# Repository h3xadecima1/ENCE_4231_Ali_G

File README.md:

# ENCE_4231_Ali_G
Embedded Systems

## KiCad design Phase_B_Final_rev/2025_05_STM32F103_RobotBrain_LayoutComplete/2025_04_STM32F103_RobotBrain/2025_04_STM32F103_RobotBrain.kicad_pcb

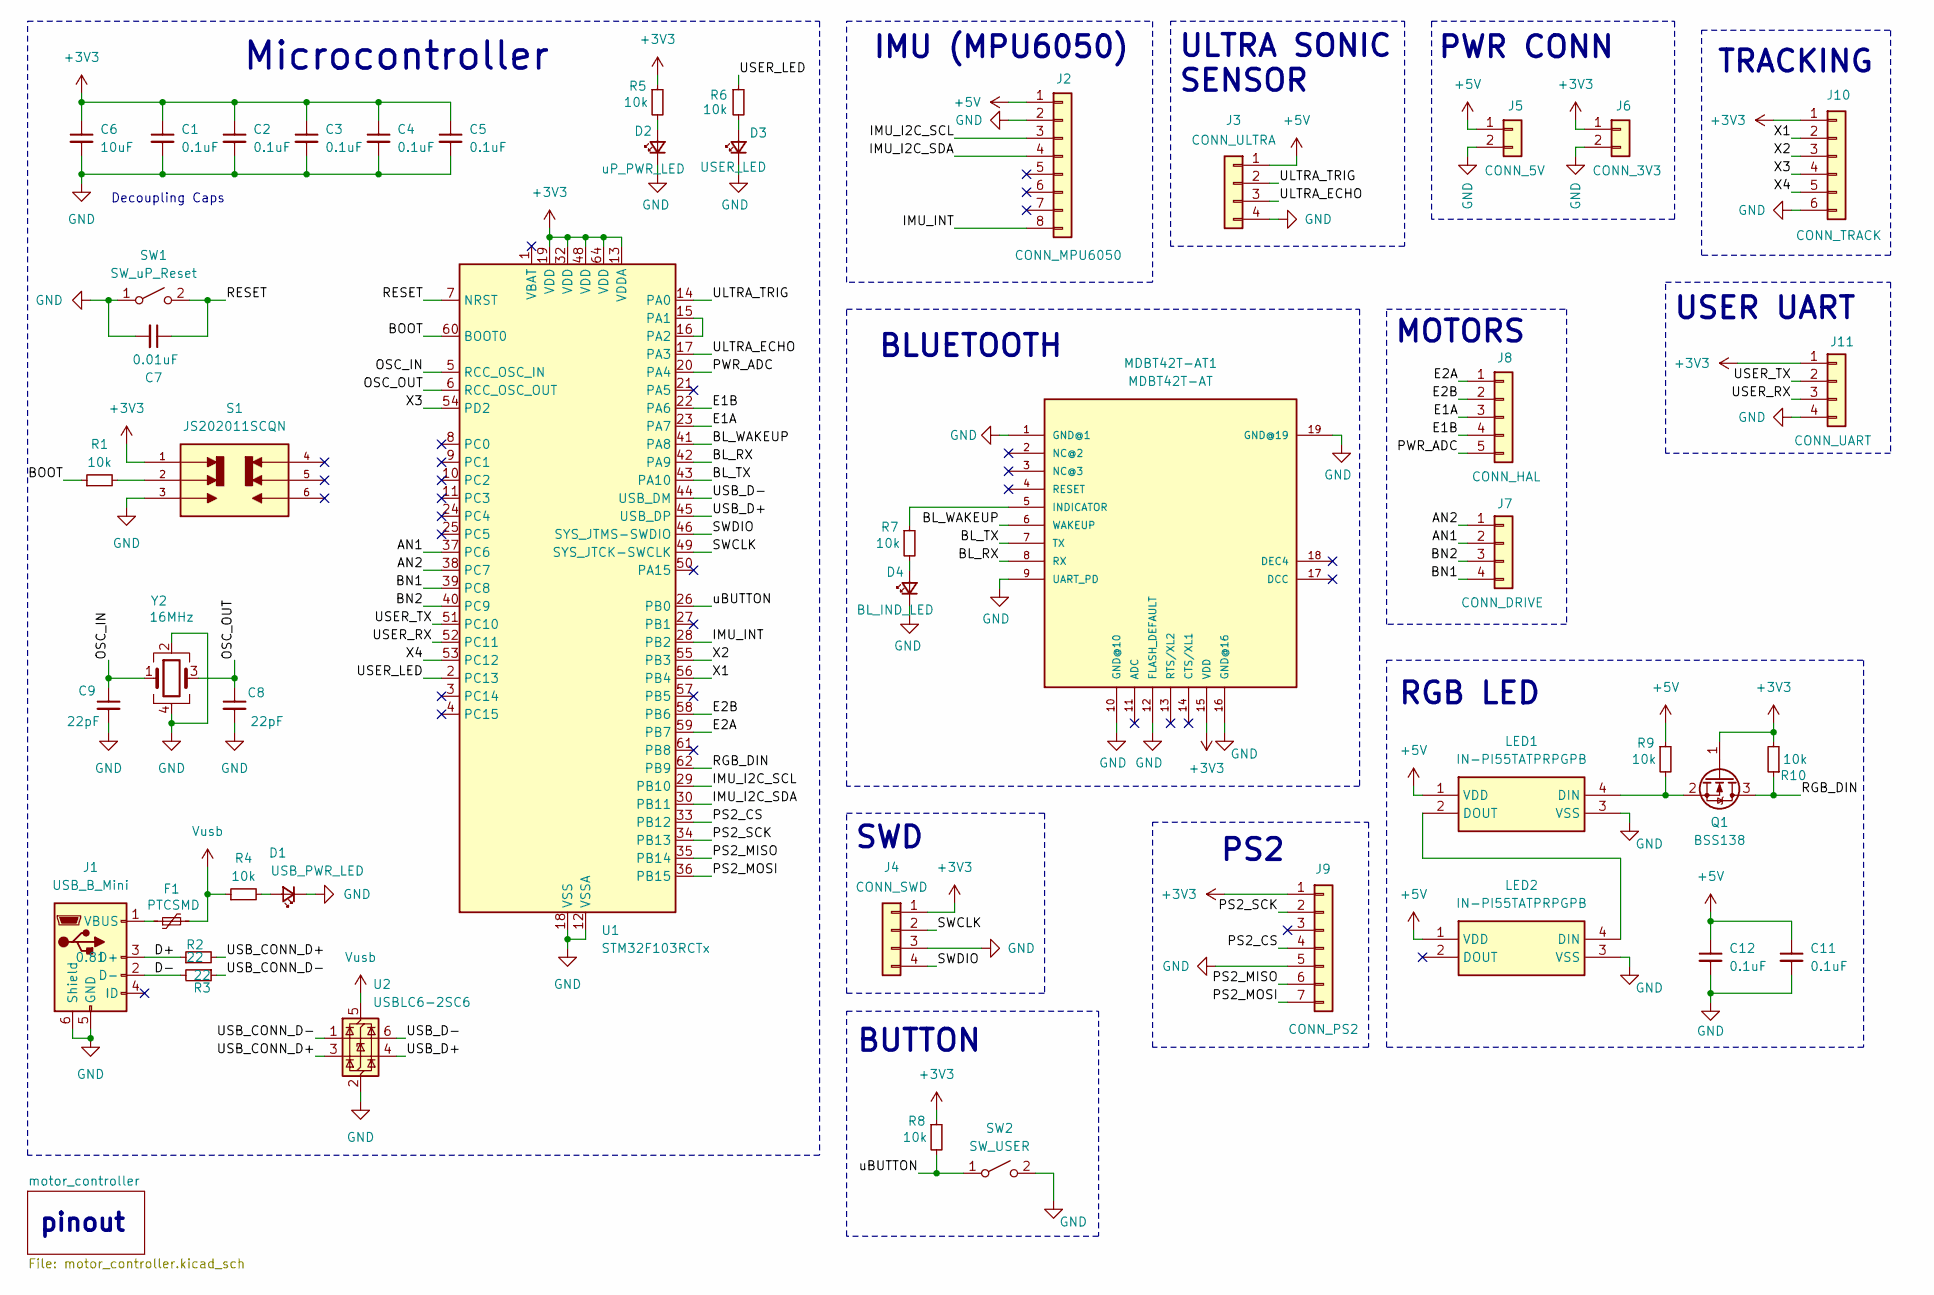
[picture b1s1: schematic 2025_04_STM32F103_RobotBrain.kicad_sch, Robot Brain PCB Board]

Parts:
C1, C2, C3, C4, C5, C11, C12: 0.1uF; C_0805_2012Metric_Pad1.18x1.45mm_HandSolder; Mfr #P KAM21BR71H104JT
C6: 10uF; C_0805_2012Metric_Pad1.18x1.45mm_HandSolder; Mfr #P LMK212ABJ106KG-T
C7: 0.01uF; C_0805_2012Metric_Pad1.18x1.45mm_HandSolder; Mfr #P KAF21BR72A103JT
C8, C9: 22pF; C_0805_2012Metric_Pad1.18x1.45mm_HandSolder; Mfr #P 0805ZA220JAT2A
D1: USB_PWR_LED; LED_0805_2012Metric_Pad1.15x1.40mm_HandSolder; Mfr #P 150080VS75000
D2: uP_PWR_LED; LED_0805_2012Metric_Pad1.15x1.40mm_HandSolder; Mfr #P 150080VS75000
D3: USER_LED; LED_0805_2012Metric_Pad1.15x1.40mm_HandSolder; Mfr #P 150080RS75000
D4: BL_IND_LED; LED_0805_2012Metric_Pad1.15x1.40mm_HandSolder; Mfr #P 150080VS75000
F1: PTCSMD; Fuse_0805_2012Metric_Pad1.15x1.40mm_HandSolder; Mfr #P 0ZCK0050AF2E
J1: USB_B_Mini; USB_Mini-B_Lumberg_2486_01_Horizontal; Mfr #P UJ2-MBH-4-SMT-TR
J2: CONN_MPU6050; PinSocket_1x08_P2.54mm_Vertical
J3: CONN_ULTRA; PinSocket_1x04_P2.54mm_Vertical
J4: CONN_SWD; PinSocket_1x04_P2.54mm_Vertical
J5: CONN_5V; JST_XH_B2B-XH-A_1x02_P2.50mm_Vertical
J6: CONN_3V3; JST_XH_B2B-XH-A_1x02_P2.50mm_Vertical
J7: CONN_DRIVE; JST_XH_B4B-XH-A_1x04_P2.50mm_Vertical
J8: CONN_HAL; JST_XH_B5B-XH-A_1x05_P2.50mm_Vertical
J9: CONN_PS2; PinHeader_1x07_P2.54mm_Vertical
J10: CONN_TRACK; JST_XH_B6B-XH-A_1x06_P2.50mm_Vertical
J11: CONN_UART; JST_XH_B4B-XH-A_1x04_P2.50mm_Vertical
LED1, LED2: IN-PI55TATPRPGPB; INPI55TATPRPGPB; Manufacturer_Part_Number IN-PI55TATPRPGPB; Mouser Part Number 743-IN-PI55TATPRPGPB
MDBT42T-AT1: MDBT42T-AT; MDBT42T
Q1: BSS138; SOT-23; Mfr #P BSS138
R1, R4, R5, R6, R7, R8, R9, R10: 10k; R_0805_2012Metric_Pad1.20x1.40mm_HandSolder; Mfr #P RK73B2ATTE103J
R2, R3: 22; R_0805_2012Metric_Pad1.20x1.40mm_HandSolder; Mfr #P RC0805FR-7W22RL
S1: JS202011SCQN; SW_uP_Boot; PARTREV 26 May 22
SW1: SW_uP_Reset; Mfr #P 434121025816
SW2: SW_USER; SW_SPST_PTS647_Sx50; Mfr #P TL3305BF100QG
U1: STM32F103RCTx; LQFP-64_10x10mm_P0.5mm; Mfr #P STM32F103RCT6
U2: USBLC6-2SC6; SOT-23-6; Mfr #P USBLC6-2SC6
Y2: 16MHz; Crystal_SMD_Abracon_ABM8G-4Pin_3.2x2.5mm; Mfr #P ABM8-16.000MHZ-D1X-T

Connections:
+3V3: C1.1, C2.1, C3.1, C4.1, C5.1, C6.1, J4.1, J6.1, J9.1, J10.1, J11.1, MDBT42T-AT1.15 (VDD), Q1.1 (G), R5.1, R8.1, R10.2, S1.1, U1.13 (VDDA), U1.19 (VDD), U1.32 (VDD), U1.48 (VDD), U1.64 (VDD)
+5V: C11.1, C12.1, J2.1, J3.1, J5.1, LED1.1 (VDD), LED2.1 (VDD), R9.1
/AN1: J7.2, U1.37 (PC6)
/AN2: J7.1, U1.38 (PC7)
/BL_RX: MDBT42T-AT1.8 (RX), U1.42 (PA9)
/BL_TX: MDBT42T-AT1.7 (TX), U1.43 (PA10)
/BL_WAKEUP: MDBT42T-AT1.6 (WAKEUP), U1.41 (PA8)
/BN1: J7.4, U1.39 (PC8)
/BN2: J7.3, U1.40 (PC9)
/BOOT: R1.1, U1.60 (BOOT0)
/D+: J1.3 (D+), R2.1
/D-: J1.2 (D-), R3.2
/E1A: J8.3, U1.23 (PA7)
/E1B: J8.4, U1.22 (PA6)
/E2A: J8.1, U1.59 (PB7)
/E2B: J8.2, U1.58 (PB6)
/IMU_I2C_SCL: J2.3, U1.29 (PB10)
/IMU_I2C_SDA: J2.4, U1.30 (PB11)
/IMU_INT: J2.8, U1.28 (PB2)
/OSC_IN: C9.1, U1.5 (RCC_OSC_IN), Y2.1
/OSC_OUT: C8.1, U1.6 (RCC_OSC_OUT), Y2.3
/PS2_CS: J9.4, U1.33 (PB12)
/PS2_MISO: J9.6, U1.35 (PB14)
/PS2_MOSI: J9.7, U1.36 (PB15)
/PS2_SCK: J9.2, U1.34 (PB13)
/PWR_ADC: J8.5, U1.20 (PA4)
/RESET: C7.1, SW1.2 (B), U1.7 (NRST)
/RGB_DIN: Q1.3 (D), R10.1, U1.62 (PB9)
/SWCLK: J4.2, U1.49 (SYS_JTCK-SWCLK)
/SWDIO: J4.4, U1.46 (SYS_JTMS-SWDIO)
/ULTRA_ECHO: J3.3, U1.17 (PA3)
/ULTRA_TRIG: J3.2, U1.14 (PA0)
/USB_CONN_D+: R2.2, U2.3 (I/O2)
/USB_CONN_D-: R3.1, U2.1 (I/O1)
/USB_D+: U1.45 (USB_DP), U2.4 (I/O2)
/USB_D-: U1.44 (USB_DM), U2.6 (I/O1)
/USER_LED: R6.1, U1.2 (PC13)
/USER_RX: J11.3, U1.52 (PC11)
/USER_TX: J11.2, U1.51 (PC10)
/X1: J10.2, U1.56 (PB4)
/X2: J10.3, U1.55 (PB3)
/X3: J10.4, U1.54 (PD2)
/X4: J10.5, U1.53 (PC12)
/uBUTTON: R8.2, SW2.1 (A), U1.26 (PB0)
GND: C1.2, C2.2, C3.2, C4.2, C5.2, C6.2, C7.2, C8.2, C9.2, C11.2, C12.2, D1.1 (K), D2.1 (K), D3.1 (K), D4.1 (K), J1.5 (GND), J1.6 (Shield), J2.2, J3.4, J4.3, J5.2, J6.2, J9.5, J10.6, J11.4, LED1.3 (VSS), LED2.3 (VSS), MDBT42T-AT1.1 (GND@1), MDBT42T-AT1.9 (UART_PD), MDBT42T-AT1.10 (GND@10), MDBT42T-AT1.12 (FLASH_DEFAULT), MDBT42T-AT1.16 (GND@16), MDBT42T-AT1.19 (GND@19), S1.3, SW1.1 (A), SW2.2 (B), U1.12 (VSSA), U1.18 (VSS), U1.31 (VSS), U1.47 (VSS), U1.63 (VSS), U2.2 (GND), Y2.2, Y2.4
unnamed: D1.2 (A), R4.2
unnamed: D2.2 (A), R5.2
unnamed: D3.2 (A), R6.2
unnamed: D4.2 (A), R7.2
unnamed: F1.1, J1.1 (VBUS)
unnamed: LED1.4 (DIN), Q1.2 (S), R9.2
unnamed: LED1.2 (DOUT), LED2.4 (DIN)
unnamed: MDBT42T-AT1.5 (INDICATOR), R7.1
unnamed: R1.2, S1.2
unnamed: U1.15 (PA1), U1.16 (PA2)
Vusb: F1.2, R4.1, U2.5 (VBUS)

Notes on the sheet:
PWR CONN
ULTRA SONIC SENSOR
Decoupling Caps
BUTTON
MOTORS
PS2
RGB LED
Microcontroller
TRACKING
pinout
IMU (MPU6050)
SWD
USER UART
BLUETOOTH

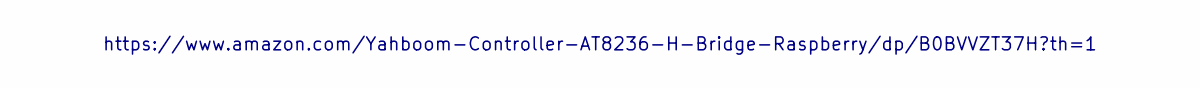
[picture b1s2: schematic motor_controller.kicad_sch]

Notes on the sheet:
https://www.amazon.com/Yahboom-Controller-AT8236-H-Bridge-Raspberry/dp/B0BVVZT37H?th=1

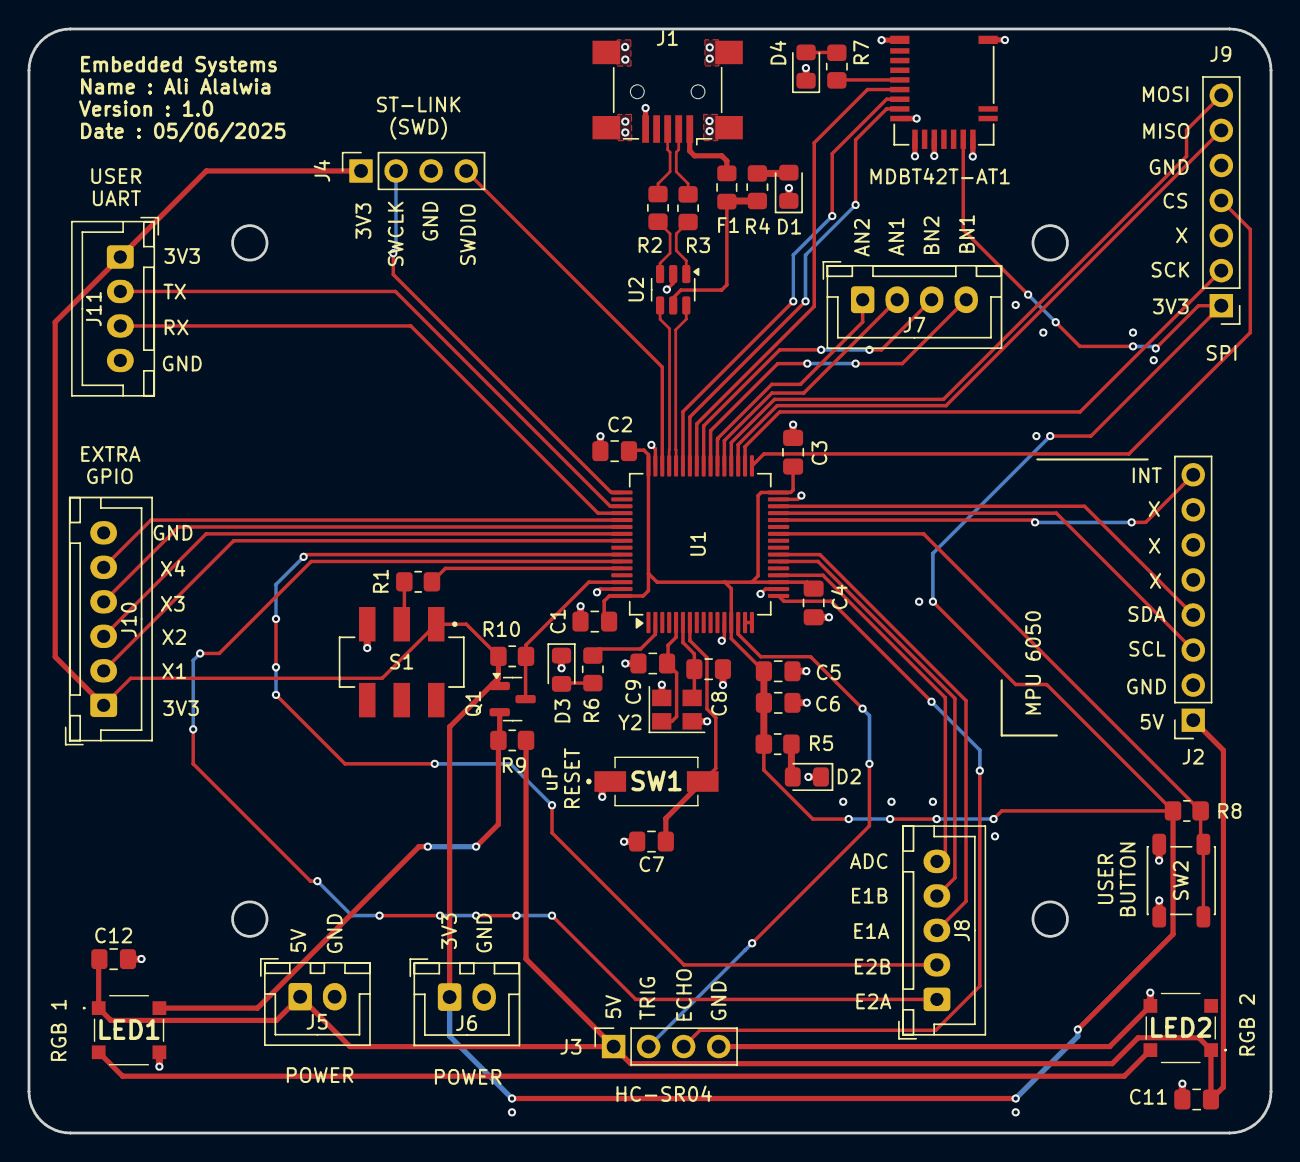
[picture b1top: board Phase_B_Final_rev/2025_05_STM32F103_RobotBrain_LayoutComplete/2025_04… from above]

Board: 2 copper layers, 90.0 x 80.0 mm, 47 parts (0 on the bottom side), 56 nets.

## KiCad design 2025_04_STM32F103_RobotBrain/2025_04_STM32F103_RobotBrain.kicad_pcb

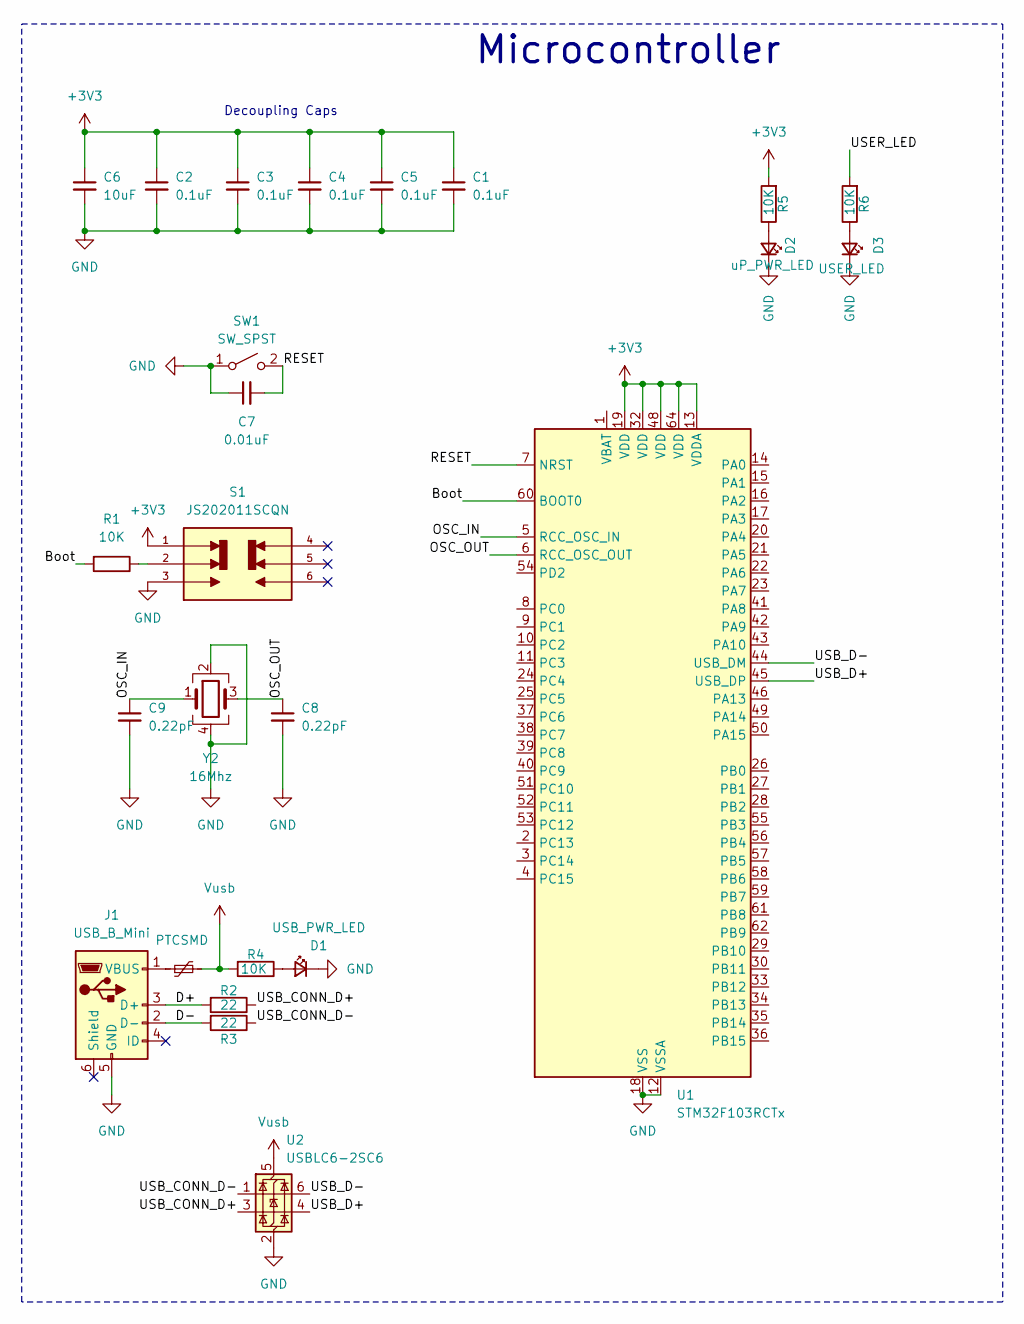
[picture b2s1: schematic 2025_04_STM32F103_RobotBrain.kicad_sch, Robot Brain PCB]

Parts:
C1, C2, C3, C4, C5: 0.1uF; C_0805_2012Metric_Pad1.18x1.45mm_HandSolder; Mfr #P KAM21BR71H104JT
C6: 10uF; C_0805_2012Metric_Pad1.18x1.45mm_HandSolder; Mfr #P LMK212ABJ106KG-T
C7: 0.01uF; C_0805_2012Metric_Pad1.18x1.45mm_HandSolder; Mfr #P KAF21BR72A103JT
C8, C9: 0.22pF; C_0805_2012Metric_Pad1.18x1.45mm_HandSolder; Mfr #P 0805YA220JAT2A
D1: USB_PWR_LED; LED_0805_2012Metric; Mfr# 150080VS75000
D2: uP_PWR_LED; LED_0805_2012Metric; Mfr# 150080VS75000
D3: USER_LED; LED_0805_2012Metric; Mfr# 150080VS75000
F1: PTCSMD; Fuse_0805_2012Metric_Pad1.15x1.40mm_HandSolder; Mfr# 0ZCK0050AF2E
J1: USB_B_Mini; USB_Mini-B_Lumberg_2486_01_Horizontal
R1, R4, R5, R6: 10K; R_0805_2012Metric_Pad1.20x1.40mm_HandSolder; Mfr# RK73B2ATTE103J
R2, R3: 22; R_0805_2012Metric_Pad1.20x1.40mm_HandSolder; Mfr# RK73B2ATTE103J
S1: JS202011SCQN; SW_up_Boot; PARTREV 26 May 22
SW1: SW_SPST; SW_uP_Reset
U1: STM32F103RCTx; LQFP-64_10x10mm_P0.5mm; Mfg #P STM32F103RCT6
U2: USBLC6-2SC6; SOT-23-6
Y2: 16Mhz; Crystal_SMD_Abracon_ABM8G-4Pin_3.2x2.5mm; Mfr# ABM8-16.000MHZ-D1X-T

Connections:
+3V3: C1.1, C2.1, C3.1, C4.1, C5.1, C6.1, R5.2, S1.1, U1.13 (VDDA), U1.19 (VDD), U1.32 (VDD), U1.48 (VDD), U1.64 (VDD)
/Boot: R1.2, U1.60 (BOOT0)
/D+: J1.3 (D+), R2.2
/D-: J1.2 (D-), R3.2
/OSC_IN: C9.1, U1.5 (RCC_OSC_IN), Y2.1
/OSC_OUT: C8.1, U1.6 (RCC_OSC_OUT), Y2.3
/RESET: C7.2, SW1.2 (B), U1.7 (NRST)
/USB_CONN_D+: R2.1, U2.3 (I/O2)
/USB_CONN_D-: R3.1, U2.1 (I/O1)
/USB_D+: U1.45 (USB_DP), U2.4 (I/O2)
/USB_D-: U1.44 (USB_DM), U2.6 (I/O1)
/USER_LED: R6.2
GND: C1.2, C2.2, C3.2, C4.2, C5.2, C6.2, C7.1, C8.2, C9.2, D1.1 (K), D2.1 (K), D3.1 (K), J1.5 (GND), S1.3, SW1.1 (A), U1.12 (VSSA), U1.18 (VSS), U1.31 (VSS), U1.47 (VSS), U1.63 (VSS), U2.2 (GND), Y2.2, Y2.4
unnamed: D1.2 (A), R4.1
unnamed: D2.2 (A), R5.1
unnamed: D3.2 (A), R6.1
unnamed: F1.1, J1.1 (VBUS)
unnamed: R1.1, S1.2
Vusb: F1.2, R4.2, U2.5 (VBUS)

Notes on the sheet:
Decoupling Caps
Microcontroller

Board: 2 copper layers, 25 parts (0 on the bottom side), 18 nets, no tracks yet.

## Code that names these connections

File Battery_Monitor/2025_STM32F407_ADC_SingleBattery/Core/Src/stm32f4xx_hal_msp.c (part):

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
    __HAL_RCC_GPIOA_CLK_ENABLE();
    /**ADC1 GPIO Configuration
    PA1     ------> ADC1_IN1
    PA4     ------> ADC1_IN4
    */
    GPIO_InitStruct.Pin = GPIO_PIN_1|GPIO_PIN_4;
    GPIO_InitStruct.Mode = GPIO_MODE_ANALOG;
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    __HAL_RCC_ADC1_CLK_DISABLE();

    /**ADC1 GPIO Configuration
    PA1     ------> ADC1_IN1
    PA4     ------> ADC1_IN4
    */
    HAL_GPIO_DeInit(GPIOA, GPIO_PIN_1|GPIO_PIN_4);

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
    __HAL_RCC_GPIOB_CLK_ENABLE();
    /**I2C1 GPIO Configuration
    PB6     ------> I2C1_SCL
    PB9     ------> I2C1_SDA
    */
    GPIO_InitStruct.Pin = Audio_SCL_Pin|Audio_SDA_Pin;
    GPIO_InitStruct.Mode = GPIO_MODE_AF_OD;
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    __HAL_RCC_I2C1_CLK_DISABLE();

    /**I2C1 GPIO Configuration
    PB6     ------> I2C1_SCL
    PB9     ------> I2C1_SDA
    */
    HAL_GPIO_DeInit(Audio_SCL_GPIO_Port, Audio_SCL_Pin);

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    __HAL_RCC_GPIOA_CLK_ENABLE();
    /**SPI1 GPIO Configuration
    PA5     ------> SPI1_SCK
    PA6     ------> SPI1_MISO
    PA7     ------> SPI1_MOSI
    */
    GPIO_InitStruct.Pin = SPI1_SCK_Pin|SPI1_MISO_Pin|SPI1_MOSI_Pin;
    GPIO_InitStruct.Mode = GPIO_MODE_AF_PP;
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
    /**SPI1 GPIO Configuration
    PA5     ------> SPI1_SCK
    PA6     ------> SPI1_MISO
    PA7     ------> SPI1_MOSI
    */
    HAL_GPIO_DeInit(GPIOA, SPI1_SCK_Pin|SPI1_MISO_Pin|SPI1_MOSI_Pin);

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
    __HAL_RCC_GPIOA_CLK_ENABLE();
    /**TIM1 GPIO Configuration
    PA8     ------> TIM1_CH1
    */
    GPIO_InitStruct.Pin = GPIO_PIN_8;
    GPIO_InitStruct.Mode = GPIO_MODE_AF_PP;
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
    __HAL_RCC_GPIOA_CLK_ENABLE();
    /**USART2 GPIO Configuration
    PA2     ------> USART2_TX
    PA3     ------> USART2_RX
    */
    GPIO_InitStruct.Pin = GPIO_PIN_2|GPIO_PIN_3;
    GPIO_InitStruct.Mode = GPIO_MODE_AF_PP;
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    __HAL_RCC_USART2_CLK_DISABLE();

    /**USART2 GPIO Configuration
    PA2     ------> USART2_TX
    PA3     ------> USART2_RX
    */
    HAL_GPIO_DeInit(GPIOA, GPIO_PIN_2|GPIO_PIN_3);

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
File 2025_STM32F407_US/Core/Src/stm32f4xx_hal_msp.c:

/* USER CODE BEGIN Header */
/**
  ******************************************************************************
  * @file         stm32f4xx_hal_msp.c
  * @brief        This file provides code for the MSP Initialization
  *               and de-Initialization codes.
  ******************************************************************************
  * @attention
  *
  * Copyright (c) 2025 STMicroelectronics.
  * All rights reserved.
  *
  * This software is licensed under terms that can be found in the LICENSE file
  * in the root directory of this software component.
  * If no LICENSE file comes with this software, it is provided AS-IS.
  *
  ******************************************************************************
  */
/* USER CODE END Header */

/* Includes ------------------------------------------------------------------*/
#include "main.h"
/* USER CODE BEGIN Includes */

/* USER CODE END Includes */

/* Private typedef -----------------------------------------------------------*/
/* USER CODE BEGIN TD */

/* USER CODE END TD */

/* Private define ------------------------------------------------------------*/
/* USER CODE BEGIN Define */

/* USER CODE END Define */

/* Private macro -------------------------------------------------------------*/
/* USER CODE BEGIN Macro */

/* USER CODE END Macro */

/* Private variables ---------------------------------------------------------*/
/* USER CODE BEGIN PV */

/* USER CODE END PV */

/* Private function prototypes -----------------------------------------------*/
/* USER CODE BEGIN PFP */

/* USER CODE END PFP */

/* External functions --------------------------------------------------------*/
/* USER CODE BEGIN ExternalFunctions */

/* USER CODE END ExternalFunctions */

/* USER CODE BEGIN 0 */

/* USER CODE END 0 */

void HAL_TIM_MspPostInit(TIM_HandleTypeDef *htim);
                    /**
  * Initializes the Global MSP.
  */
void HAL_MspInit(void)
{

  /* USER CODE BEGIN MspInit 0 */

  /* USER CODE END MspInit 0 */

  __HAL_RCC_SYSCFG_CLK_ENABLE();
  __HAL_RCC_PWR_CLK_ENABLE();

  HAL_NVIC_SetPriorityGrouping(NVIC_PRIORITYGROUP_0);

  /* System interrupt init*/

  /* USER CODE BEGIN MspInit 1 */

  /* USER CODE END MspInit 1 */
}

/**
  * @brief TIM_Base MSP Initialization
  * This function configures the hardware resources used in this example
  * @param htim_base: TIM_Base handle pointer
  * @retval None
  */
void HAL_TIM_Base_MspInit(TIM_HandleTypeDef* htim_base)
{
  GPIO_InitTypeDef GPIO_InitStruct = {0};
  if(htim_base->Instance==TIM8)
  {
    /* USER CODE BEGIN TIM8_MspInit 0 */

    /* USER CODE END TIM8_MspInit 0 */
    /* Peripheral clock enable */
    __HAL_RCC_TIM8_CLK_ENABLE();

    __HAL_RCC_GPIOC_CLK_ENABLE();
    /**TIM8 GPIO Configuration
    PC6     ------> TIM8_CH1
    PC7     ------> TIM8_CH2
    */
    GPIO_InitStruct.Pin = ECHO_Pin|GPIO_PIN_7;
    GPIO_InitStruct.Mode = GPIO_MODE_AF_PP;
    GPIO_InitStruct.Pull = GPIO_NOPULL;
    GPIO_InitStruct.Speed = GPIO_SPEED_FREQ_LOW;
    GPIO_InitStruct.Alternate = GPIO_AF3_TIM8;
    HAL_GPIO_Init(GPIOC, &GPIO_InitStruct);

    /* USER CODE BEGIN TIM8_MspInit 1 */

    /* USER CODE END TIM8_MspInit 1 */
  }
  else if(htim_base->Instance==TIM11)
  {
    /* USER CODE BEGIN TIM11_MspInit 0 */

    /* USER CODE END TIM11_MspInit 0 */
    /* Peripheral clock enable */
    __HAL_RCC_TIM11_CLK_ENABLE();
    /* TIM11 interrupt Init */
    HAL_NVIC_SetPriority(TIM1_TRG_COM_TIM11_IRQn, 0, 0);
    HAL_NVIC_EnableIRQ(TIM1_TRG_COM_TIM11_IRQn);
    /* USER CODE BEGIN TIM11_MspInit 1 */

    /* USER CODE END TIM11_MspInit 1 */
  }

}

void HAL_TIM_MspPostInit(TIM_HandleTypeDef* htim)
{
  GPIO_InitTypeDef GPIO_InitStruct = {0};
  if(htim->Instance==TIM11)
  {
    /* USER CODE BEGIN TIM11_MspPostInit 0 */

    /* USER CODE END TIM11_MspPostInit 0 */

    __HAL_RCC_GPIOB_CLK_ENABLE();
    /**TIM11 GPIO Configuration
    PB9     ------> TIM11_CH1
    */
    GPIO_InitStruct.Pin = TRIG_Pin;
    GPIO_InitStruct.Mode = GPIO_MODE_AF_PP;
    GPIO_InitStruct.Pull = GPIO_NOPULL;
    GPIO_InitStruct.Speed = GPIO_SPEED_FREQ_LOW;
    GPIO_InitStruct.Alternate = GPIO_AF3_TIM11;
    HAL_GPIO_Init(TRIG_GPIO_Port, &GPIO_InitStruct);

    /* USER CODE BEGIN TIM11_MspPostInit 1 */

    /* USER CODE END TIM11_MspPostInit 1 */
  }

}
/**
  * @brief TIM_Base MSP De-Initialization
  * This function freeze the hardware resources used in this example
  * @param htim_base: TIM_Base handle pointer
  * @retval None
  */
void HAL_TIM_Base_MspDeInit(TIM_HandleTypeDef* htim_base)
{
  if(htim_base->Instance==TIM8)
  {
    /* USER CODE BEGIN TIM8_MspDeInit 0 */

    /* USER CODE END TIM8_MspDeInit 0 */
    /* Peripheral clock disable */
    __HAL_RCC_TIM8_CLK_DISABLE();

    /**TIM8 GPIO Configuration
    PC6     ------> TIM8_CH1
    PC7     ------> TIM8_CH2
    */
    HAL_GPIO_DeInit(GPIOC, ECHO_Pin|GPIO_PIN_7);

    /* USER CODE BEGIN TIM8_MspDeInit 1 */

    /* USER CODE END TIM8_MspDeInit 1 */
  }
  else if(htim_base->Instance==TIM11)
  {
    /* USER CODE BEGIN TIM11_MspDeInit 0 */

    /* USER CODE END TIM11_MspDeInit 0 */
    /* Peripheral clock disable */
    __HAL_RCC_TIM11_CLK_DISABLE();

    /* TIM11 interrupt DeInit */
    HAL_NVIC_DisableIRQ(TIM1_TRG_COM_TIM11_IRQn);
    /* USER CODE BEGIN TIM11_MspDeInit 1 */

    /* USER CODE END TIM11_MspDeInit 1 */
  }

}

/**
  * @brief UART MSP Initialization
  * This function configures the hardware resources used in this example
  * @param huart: UART handle pointer
  * @retval None
  */
void HAL_UART_MspInit(UART_HandleTypeDef* huart)
{
  GPIO_InitTypeDef GPIO_InitStruct = {0};
  if(huart->Instance==USART2)
  {
    /* USER CODE BEGIN USART2_MspInit 0 */

    /* USER CODE END USART2_MspInit 0 */
    /* Peripheral clock enable */
    __HAL_RCC_USART2_CLK_ENABLE();

    __HAL_RCC_GPIOA_CLK_ENABLE();
    /**USART2 GPIO Configuration
    PA2     ------> USART2_TX
    PA3     ------> USART2_RX
    */
    GPIO_InitStruct.Pin = GPIO_PIN_2|GPIO_PIN_3;
    GPIO_InitStruct.Mode = GPIO_MODE_AF_PP;
    GPIO_InitStruct.Pull = GPIO_NOPULL;
    GPIO_InitStruct.Speed = GPIO_SPEED_FREQ_VERY_HIGH;
    GPIO_InitStruct.Alternate = GPIO_AF7_USART2;
    HAL_GPIO_Init(GPIOA, &GPIO_InitStruct);

    /* USER CODE BEGIN USART2_MspInit 1 */

    /* USER CODE END USART2_MspInit 1 */

  }

}

/**
  * @brief UART MSP De-Initialization
  * This function freeze the hardware resources used in this example
  * @param huart: UART handle pointer
  * @retval None
  */
void HAL_UART_MspDeInit(UART_HandleTypeDef* huart)
{
  if(huart->Instance==USART2)
  {
    /* USER CODE BEGIN USART2_MspDeInit 0 */

    /* USER CODE END USART2_MspDeInit 0 */
    /* Peripheral clock disable */
    __HAL_RCC_USART2_CLK_DISABLE();

    /**USART2 GPIO Configuration
    PA2     ------> USART2_TX
    PA3     ------> USART2_RX
    */
    HAL_GPIO_DeInit(GPIOA, GPIO_PIN_2|GPIO_PIN_3);

    /* USER CODE BEGIN USART2_MspDeInit 1 */

    /* USER CODE END USART2_MspDeInit 1 */
  }

}

/* USER CODE BEGIN 1 */

/* USER CODE END 1 */

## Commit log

2025-04-22 Read Me
2025-04-22 Ultrasonic_Sensor_Challenge
2025-04-29 Robotbrain
2025-05-06 Robotbrain_final_rev
2025-05-20 Battery_Monitor
2025-05-20 Battery_Monitor v2.0
